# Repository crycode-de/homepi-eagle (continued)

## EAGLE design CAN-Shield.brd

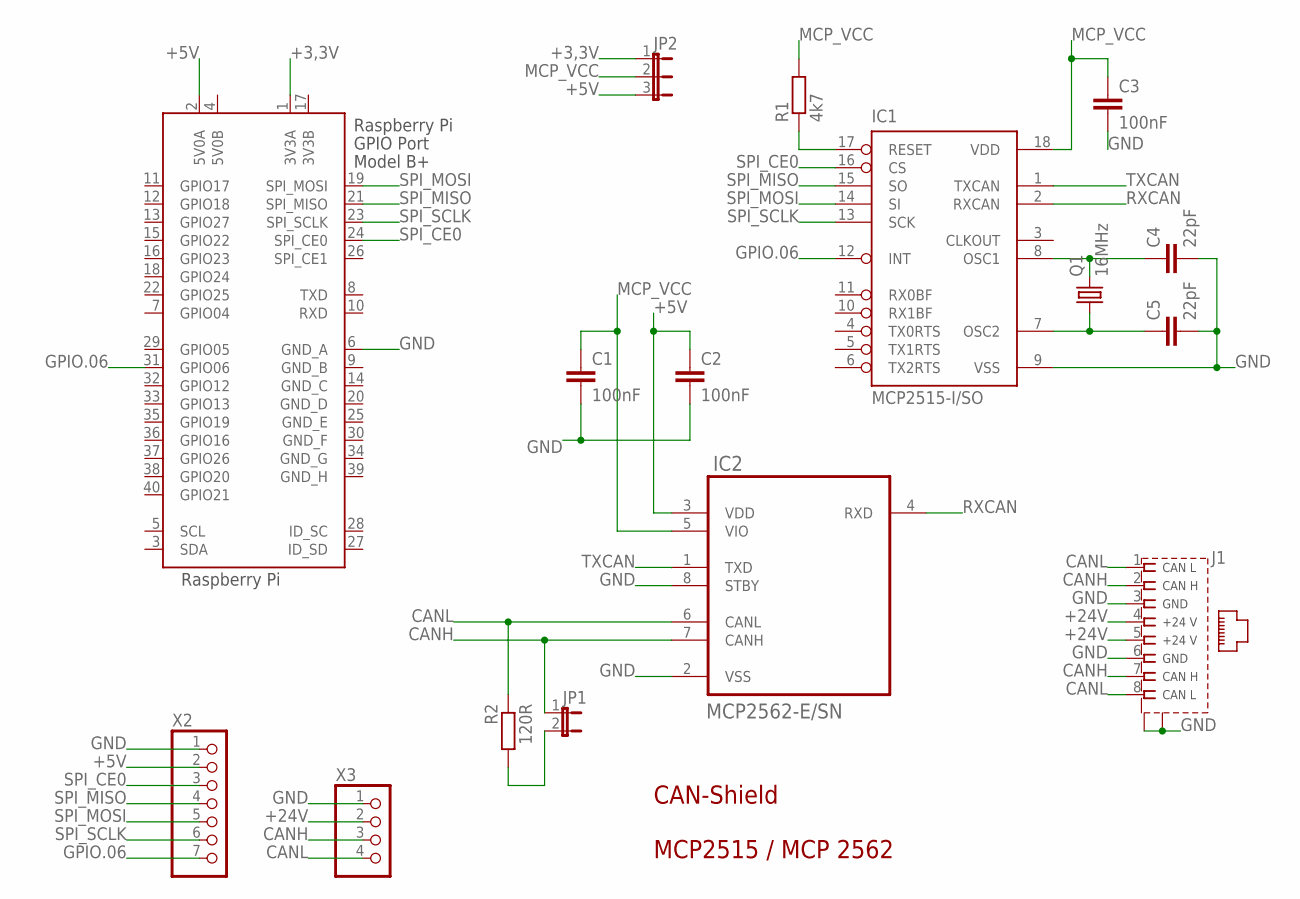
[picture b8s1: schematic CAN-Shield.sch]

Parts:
C1, C2, C3: 100nF; C1206
C4, C5: 22pF; C1206
IC1: MCP2515-I/SO; SO18L
IC2: MCP2562-E/SN; SO08
J1: RJ45-CAN; MEBP_8-8G
JP1: JP1E; JP1
JP2: JP2E; JP2
Q1: 16MHz; HC49UP
R1: 4k7; R1206
R2: 120R; R1206
X1: RASPI_GPIO_B+#_PIN; RASPI_GPIO_B+_PIN
X2: PINHD-1X7; 1X07
X3: PINHD-1X4; 1X04

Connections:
3V3B: X1.17 (3V3B)
5V0B: X1.4 (5V0B)
+3,3V: JP2.1, X1.1 (3V3A)
+5V: C2.1, IC2.3 (VDD), JP2.3, X1.2 (5V0A), X2.2
+24V: J1.4, J1.5, X3.2
CANH: IC2.7 (CANH), J1.2, J1.7, JP1.1, X3.3
CANL: IC2.6 (CANL), J1.1, J1.8, R2.1, X3.4
GND: C1.2, C2.2, C3.2, C4.2, C5.2, IC1.9 (VSS), IC2.2 (VSS), IC2.8 (STBY), J1.3, J1.6, J1.G1 (S1), J1.G2 (S2), X1.6 (GND_A), X2.1, X3.1
GND_B: X1.9 (GND_B)
GND_C: X1.14 (GND_C)
GND_D: X1.20 (GND_D)
GND_E: X1.25 (GND_E)
GND_F: X1.30 (GND_F)
GND_G: X1.34 (GND_G)
GND_H: X1.39 (GND_H)
GPIO.06: IC1.12 (INT), X1.31 (GPIO06), X2.7
MCP_VCC: C1.1, C3.1, IC1.18 (VDD), IC2.5 (VIO), JP2.2, R1.2
unnamed: C4.1, IC1.8 (OSC1), Q1.2
unnamed: IC1.17 (RESET), R1.1
unnamed: JP1.2, R2.2
unnamed: C5.1, IC1.7 (OSC2), Q1.1
RXCAN: IC1.2 (RXCAN), IC2.4 (RXD)
SPI_CE0: IC1.16 (CS), X1.24 (SPI_CE0), X2.3
SPI_MISO: IC1.15 (SO), X1.21 (SPI_MISO), X2.4
SPI_MOSI: IC1.14 (SI), X1.19 (SPI_MOSI), X2.5
SPI_SCLK: IC1.13 (SCK), X1.23 (SPI_SCLK), X2.6
TXCAN: IC1.1 (TXCAN), IC2.1 (TXD)

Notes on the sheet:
CAN-Shield MCP2515 / MCP 2562
Raspberry Pi

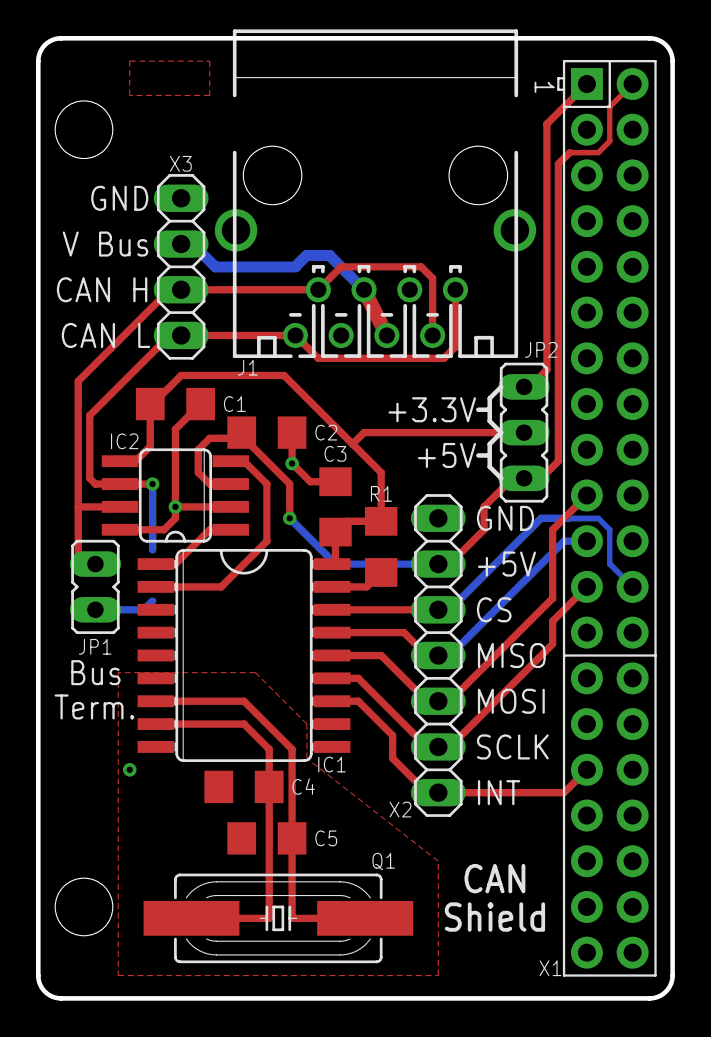
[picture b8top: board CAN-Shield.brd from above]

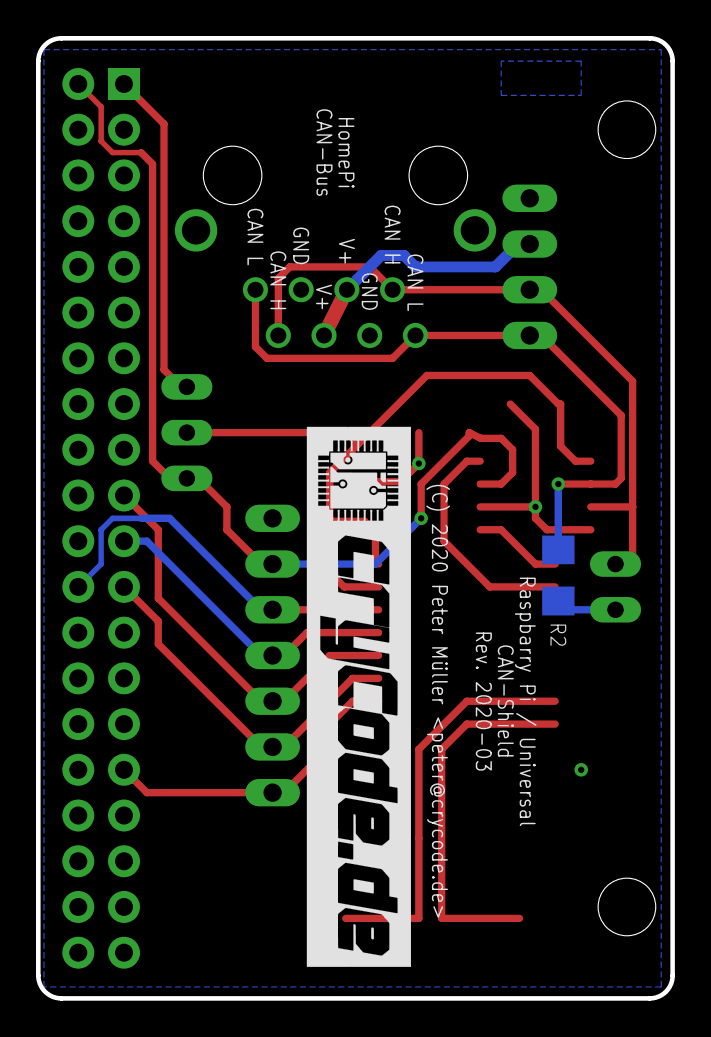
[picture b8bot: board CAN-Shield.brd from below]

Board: 2 copper layers, 35.2 x 53.3 mm, 17 parts (2 on the bottom side), 18 nets.

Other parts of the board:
U$1: 30MM

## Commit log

2016-01-16 Eagle Projekt hinzugefügt
2016-02-05 Pulldown-Widerstände zwichen Optokopplern und Logik-ICs hinzugefügt
2016-07-25 IO-Board
2016-07-29 IO-Board angepasst, 433MHz-Sender hinzugefügt
2016-07-29 Markise-Relais und IO-Board-2, neu IO-Board angepasst
2016-07-30 433MHz-Server und IO-Board-2 Anpassungen
2016-08-03 IO-Board und IO-Board-2 Anpassungen
2016-08-04 IO-Board-2 Anpassung
2016-08-04 Teileliste
2016-08-06 Teileliste Reichelt
2019-03-15 Pi und Stromversorgung Rev. 2019
2019-03-17 Anpassungen an Rev. 2019, erste Can-Bus Elemente
2019-03-18 .gitignore angepasst, eagle.epf aus Git Repo entfernt
2019-03-18 Can-Bus, Reset für den RasPi, Kleinere Optimierungen
2019-03-24 3,3V-Versorgung nur noch über TSR-Spannungsregler
2019-03-24 1-Wire Sensor auf Raspi-Platine
2019-03-29 Diverse Anpassungen
2019-03-31 Pi, CanBus, Stromversorgung, Steckverbinder angepasst
2019-04-01 Platinen angepasst, Backplane
2019-04-05 Pi-Display hinzugefügt, Boards angepasst
2019-04-09 CanBus-Forward und -Y hinzugefügt, Neues Layout für Pi-Display-2
2019-04-12 Layouts aktualisiert, Neue Libs
2019-04-14 Layouts angepasst
2019-04-16 CAN-Bus Beadboard-Adapter, Layouts angepasst
2019-04-30 Layouts angepasst, Backplane vergrößert
2019-05-06 Leiterplatten verkleinert zur Kostenerspranis
2019-08-21 Schaltpläne aufgehübscht zur Veröffentlichung
2019-08-21 Readme und Lizenz hinzugefügt
2019-08-21 Beschriftung hinzugefügt
2019-08-23 Zusätzliche Kondensatoren auf CAN-Hat gegen Reset beim Einschalten des Pis
2019-08-29 Schaltplanauszug zum CAN-Bus am RasPi hinzugefügt
2020-02-09 Added CAN-Bus UP-Schalter
2020-02-09 Updated CAN-Bus UP-Schalter
2020-03-03 CAN-Schield hinzugefügt, CanBus-UP-Schalter fertiggestellt
2020-04-17 CanBus-UP-Schalter fertiggestellt
2020-04-26 Verbesserte Stromversorgung, Pi-Kühler, CAN-Bus 8x-Schalter
2020-04-29 Werte von Bauteilen angepasst
2020-05-17 CAN-Bus Gartenbewässerung
2021-02-25 Schaltpläne optimiert
2021-02-25 Readme und Lizenz aktualisiert, Schaltpläne optimiert
2021-02-25 GitHub funding hinzugefügt
2021-02-25 Readme angepasst
2024-06-19 CAN-Bus 8x-Schalter CS PullUp hinzugefügt
2024-06-19 Readme aktualisiert
